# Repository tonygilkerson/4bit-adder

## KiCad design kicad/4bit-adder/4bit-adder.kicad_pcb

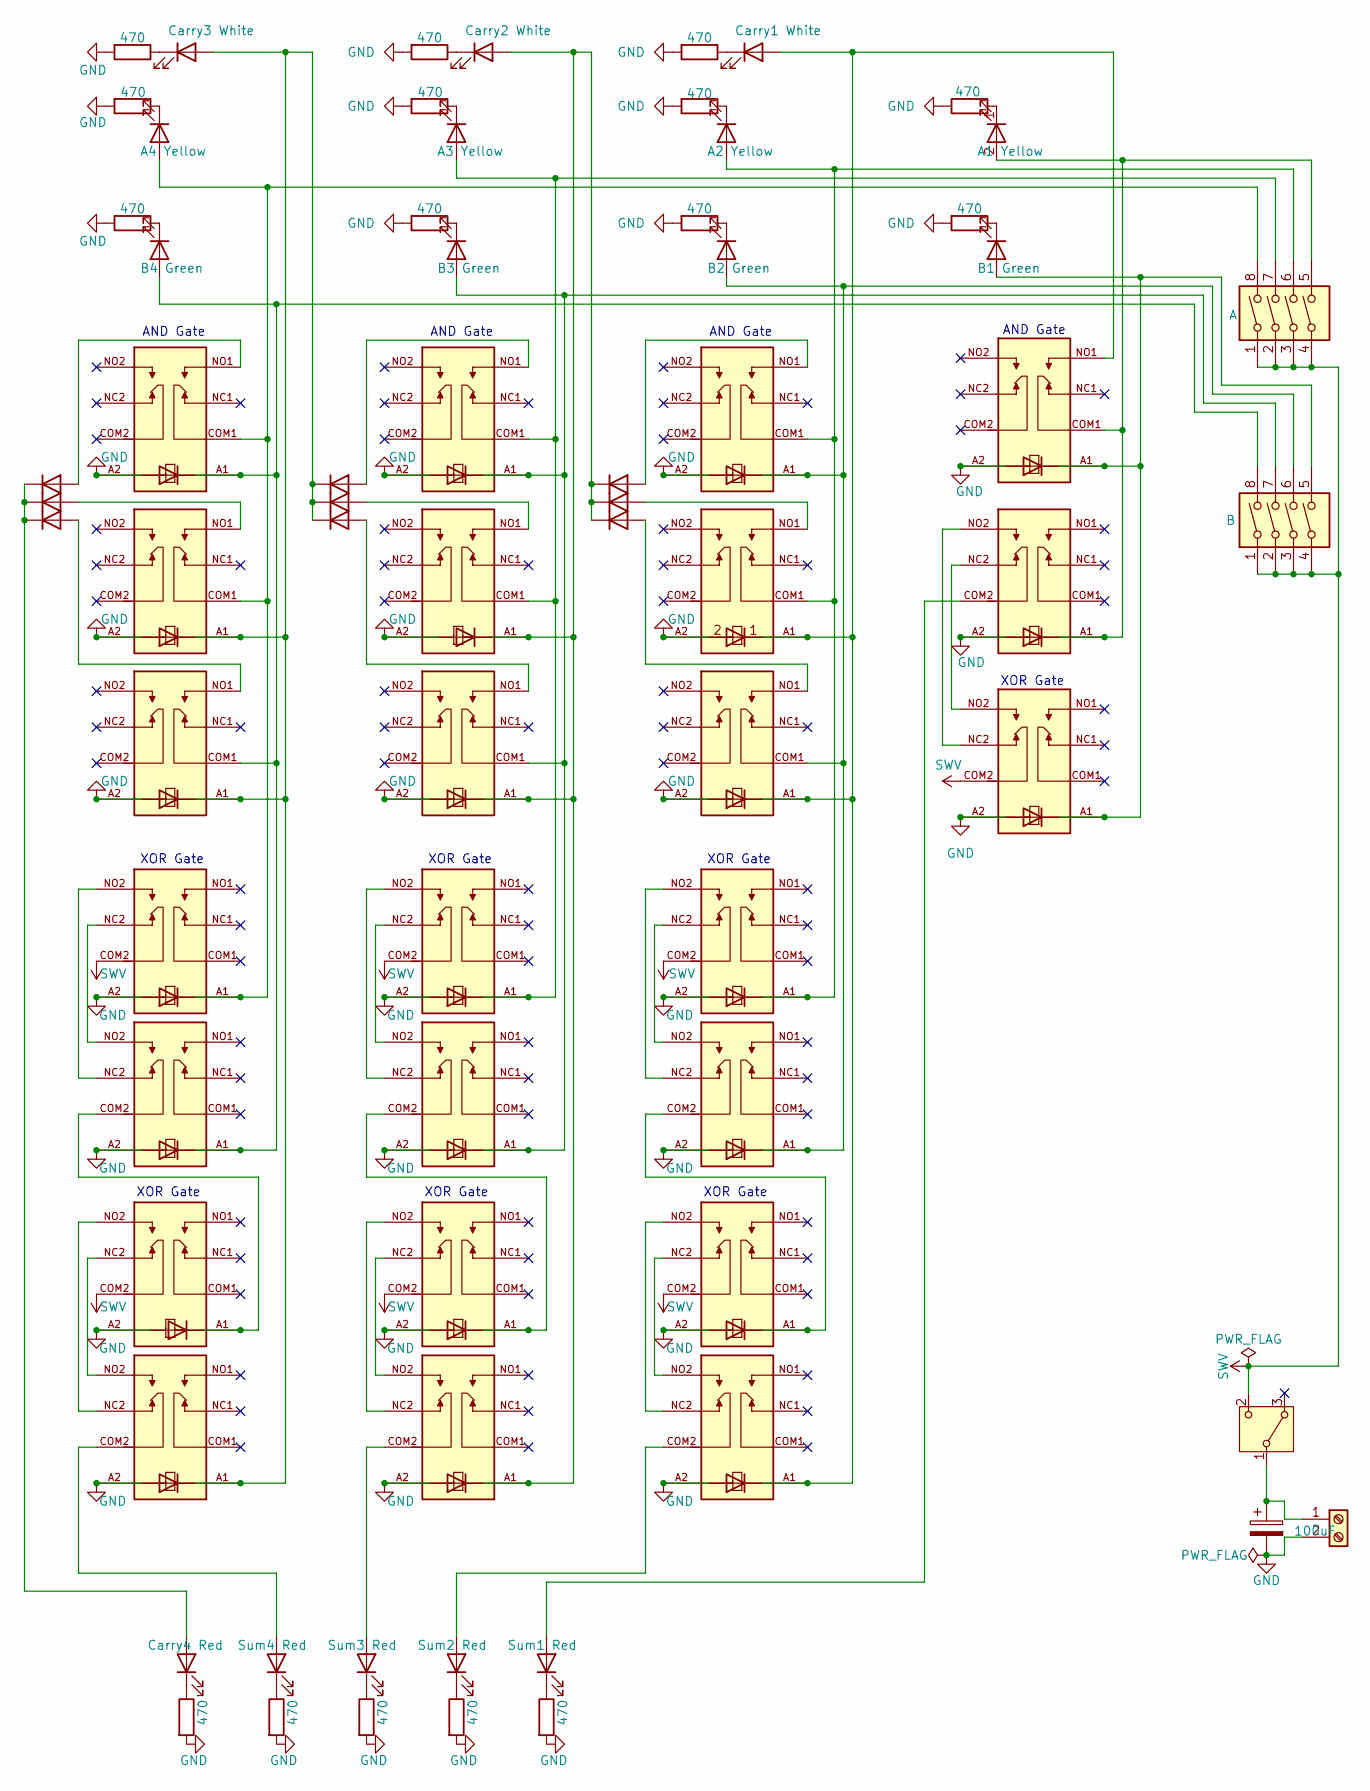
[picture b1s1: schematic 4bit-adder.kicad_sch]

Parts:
C1: 100uF; CP_Radial_D10.0mm_P2.50mm
D1, D3, D4, D5, D6, D7, D22, D23, D24, D26, D27, D28, D29, D30, D31, D32, D33, D34, D35, D36, D37, D38, D39, D40, D41, D42, D43, D44, D45, D46, D47, D48, D49: 1N4001; D_T-1_P5.08mm_Horizontal
D2: A1 Yellow; LED_D3.0mm
D8: Sum1 Red; LED_D3.0mm
D9: Carry1 White; LED_D3.0mm
D10: A4 Yellow; LED_D3.0mm
D11: Carry2 White; LED_D3.0mm
D12: Carry3 White; LED_D3.0mm
D13: Sum2 Red; LED_D3.0mm
D14: Sum3 Red; LED_D3.0mm
D15: B4 Green; LED_D3.0mm
D16: A3 Yellow; LED_D3.0mm
D17: B3 Green; LED_D3.0mm
D18: A2 Yellow; LED_D3.0mm
D19: B2 Green; LED_D3.0mm
D20: Sum4 Red; LED_D3.0mm
D21: B1 Green; LED_D3.0mm
D25: Carry4 Red; LED_D3.0mm
J1: Screw_Terminal_01x02; TerminalBlock_MaiXu_MX126-5.0-02P_1x02_P5.00mm
K1, K2, K3, K4, K5, K6, K7, K8, K9, K10, K11, K12, K13, K14, K15, K16, K17, K18, K19, K20, K21, K22, K23, K24: SR11-5V-200-2C-PH; RELAY_SR11-5V-200-2C; PARTREV 1.01
R2, R8, R9, R10, R11, R12, R13, R15, R16, R17, R18, R19, R20, R21, R22, R23: 470; R_Axial_DIN0207_L6.3mm_D2.5mm_P10.16mm_Horizontal
SW1: SW_Wuerth_450301014042; SW_Slide-03_Wuerth-WS-SLTV_10x2.5x6.4_P2.54mm
SW3: A; SW_DIP_SPSTx04_Piano_10.8x11.72mm_W7.62mm_P2.54mm
SW4: B; SW_DIP_SPSTx04_Piano_10.8x11.72mm_W7.62mm_P2.54mm

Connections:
GND: C1.2, D26.2 (A), D27.2 (A), D28.2 (A), D29.2 (A), D30.2 (A), D31.2 (A), D32.2 (A), D33.2 (A), D34.2 (A), D35.2 (A), D36.2 (A), D37.2 (A), D38.2 (A), D39.2 (A), D40.2 (A), D41.2 (A), D42.2 (A), D43.2 (A), D44.2 (A), D45.2 (A), D46.2 (A), D47.2 (A), D48.2 (A), D49.2 (A), J1.2, K1.A2, K2.A2, K3.A2, K4.A2, K5.A2, K6.A2, K7.A2, K8.A2, K9.A2, K10.A2, K11.A2, K12.A2, K13.A2, K14.A2, K15.A2, K16.A2, K17.A2, K18.A2, K19.A2, K20.A2, K21.A2, K22.A2, K23.A2, K24.A2, R2.1, R8.2, R9.2, R10.2, R11.2, R12.2, R13.2, R15.2, R16.2, R17.2, R18.2, R19.2, R20.2, R21.2, R22.2, R23.2
unnamed: D1.2 (A), K1.NO1
unnamed: D1.1 (K), D3.1 (K), D4.1 (K), D11.2 (A), D35.1 (K), D44.1 (K), D45.1 (K), K11.A1, K12.A1, K18.A1
unnamed: D2.2 (A), D27.1 (K), K7.COM1, K8.A1, SW3.5
unnamed: D2.1 (K), R2.2
unnamed: D3.2 (A), K2.NO1
unnamed: D4.2 (A), K3.NO1
unnamed: D5.2 (A), K10.NO1
unnamed: D6.2 (A), K11.NO1
unnamed: D7.2 (A), K12.NO1
unnamed: D8.2 (A), K8.COM2
unnamed: D8.1 (K), R8.1
unnamed: D9.1 (K), R20.1
unnamed: D10.2 (A), D42.1 (K), K16.COM1, K19.COM1, K21.A1, SW3.8
unnamed: D10.1 (K), R10.1
unnamed: D11.1 (K), R22.1
unnamed: D5.1 (K), D6.1 (K), D7.1 (K), D12.2 (A), D36.1 (K), D43.1 (K), D46.1 (K), K19.A1, K20.A1, K24.A1
unnamed: D12.1 (K), R23.1
unnamed: D13.2 (A), K17.COM2
unnamed: D13.1 (K), R9.1
unnamed: D14.2 (A), K18.COM2
unnamed: D14.1 (K), R11.1
unnamed: D15.2 (A), D40.1 (K), D47.1 (K), K16.A1, K20.COM1, K22.A1, SW4.8
unnamed: D15.1 (K), R15.1
unnamed: D16.2 (A), D41.1 (K), K10.COM1, K11.COM1, K13.A1, SW3.7
unnamed: D16.1 (K), R16.1
unnamed: D17.2 (A), D39.1 (K), D48.1 (K), K10.A1, K12.COM1, K14.A1, SW4.7
unnamed: D17.1 (K), R17.1
unnamed: D18.2 (A), D32.1 (K), K1.COM1, K2.COM1, K4.A1, SW3.6
unnamed: D18.1 (K), R18.1
unnamed: D19.2 (A), D29.1 (K), D33.1 (K), K1.A1, K3.COM1, K5.A1, SW4.6
unnamed: D19.1 (K), R19.1
unnamed: D20.2 (A), K24.COM2
unnamed: D20.1 (K), R12.1
unnamed: D21.2 (A), D26.1 (K), D28.1 (K), K7.A1, K9.A1, SW4.5
unnamed: D21.1 (K), R21.1
unnamed: D22.2 (A), K16.NO1
unnamed: D22.1 (K), D23.1 (K), D24.1 (K), D25.2 (A)
unnamed: D23.2 (A), K19.NO1
unnamed: D24.2 (A), K20.NO1
unnamed: D25.1 (K), R13.1
unnamed: D9.2 (A), D30.1 (K), D31.1 (K), D34.1 (K), K2.A1, K3.A1, K7.NO1, K17.A1
unnamed: D37.1 (K), K22.COM2, K23.A1
unnamed: D38.1 (K), K14.COM2, K15.A1
unnamed: D49.1 (K), K5.COM2, K6.A1
unnamed: C1.1, J1.1, SW1.1 (B)
unnamed: K4.NC2, K5.NO2
unnamed: K4.NO2, K5.NC2
unnamed: K8.NC2, K9.NO2
unnamed: K8.NO2, K9.NC2
unnamed: K13.NC2, K14.NO2
unnamed: K13.NO2, K14.NC2
unnamed: K15.NC2, K18.NO2
unnamed: K15.NO2, K18.NC2
unnamed: K6.NO2, K17.NC2
unnamed: K6.NC2, K17.NO2
unnamed: K21.NC2, K22.NO2
unnamed: K21.NO2, K22.NC2
unnamed: K23.NC2, K24.NO2
unnamed: K23.NO2, K24.NC2
SWV: K4.COM2, K6.COM2, K9.COM2, K13.COM2, K15.COM2, K21.COM2, K23.COM2, SW1.2 (C), SW3.1, SW3.2, SW3.3, SW3.4, SW4.1, SW4.2, SW4.3, SW4.4

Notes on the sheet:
AND Gate
XOR Gate

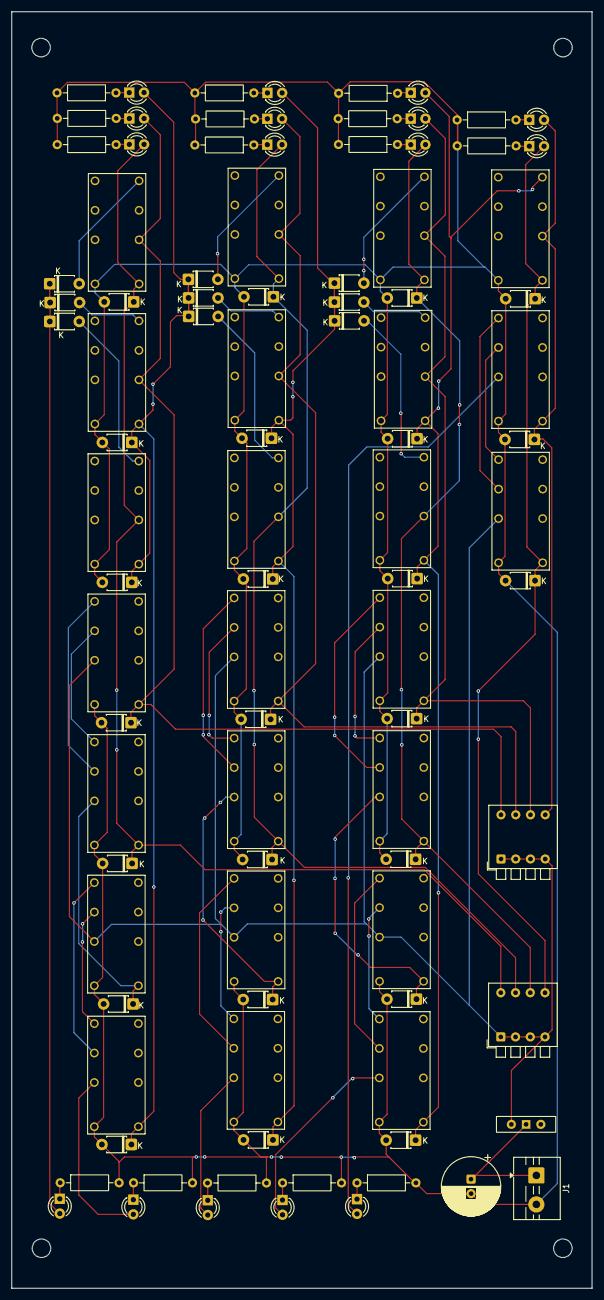
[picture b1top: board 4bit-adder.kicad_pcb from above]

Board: 2 copper layers, 100.1 x 220.1 mm, 94 parts (0 on the bottom side), 61 nets.

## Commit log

2026-04-11 initial layout
2026-04-13 relay image
2026-05-18 start kicad schema
2026-05-19 half adder schema
2026-05-20 wip schema
2026-05-21 schematic first draft
2026-05-23 initial pcb layout
2026-05-25 footprints initial layout
2026-05-25 wired top pad-A
2026-05-26 finished pcb wiring
2026-05-27 more pbc
2026-06-09 user manual fig1
